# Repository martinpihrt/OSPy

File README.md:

OSPy

###### **O**pen **S**prinkler **Py**thon
OSPy is a free Raspberry Pi based Python 3 program for controlling irrigation systems (sprinkler, drip, IoT, etc). This is my fork from [Rimco/OSPy](https://github.com/Rimco/OSPy) and [Dan-in-CA/SIP](https://github.com/Dan-in-CA/SIP) with My modifications.  

## For first installation and other visit 
[Clean installation](https://github.com/martinpihrt/OSPy/tree/master/ospy/docs/Clean_installation.md)

## Mobile App [Google store](https://play.google.com/store/apps/details?id=com.pihrt.ospy.mobile)

Paired phones and immediate push notifications are managed in **Options → Mobile applications**. Push delivery is disabled by default; the editable relay field is prefilled with the official OSPy relay URL. OSPy sends signed, installation-scoped events asynchronously to the HTTPS relay, which delivers them through Firebase Cloud Messaging. Firebase credentials and FCM device tokens are never stored in OSPy. See the [Mobile API v1 push notification reference](api/docs/Mobile_API_v1.md#immediate-push-notifications).

Normal mobile communication is direct: the Android application connects to the saved local or remote OSPy HTTPS address and uses installation-scoped Mobile API v1 access and refresh tokens to read state and perform permitted actions. Immediate push is a separate background path: OSPy signs an asynchronous request to the configured relay, which validates it and delivers through Firebase Cloud Messaging even while the application is closed. Relay failure cannot block irrigation scheduling or outputs. Both flows are shown in **Diagnostics → How OSPy works**.

The common OSPy footer contains a direct link to the official Android application in Google Play.

When anonymous usage statistics are enabled, OSPy reports the installation UUID, version and non-identifying platform details. On Raspberry Pi it also sends a SHA-256 pseudonym derived locally from the board serial so a reinstallation or replacement SD card is not counted as new hardware. The raw board serial is never transmitted, and systems without a trustworthy board serial omit the hardware identifier.

Refresh-token rotation includes a single short recovery retry for a mobile process terminated between receiving and durably saving its replacement token, such as during a Google Play application update. This preserves saved connections without weakening explicit logout or administrator device revocation.

On supported Android and Google Play services versions, the application also registers a Restore Credential after a successful sign-in. A replacement phone can use the end-to-end encrypted restore key to request a new OSPy token session; passwords, 2FA codes and API tokens are never included in Android backup. OSPy accepts only the production Play signing origin for `com.pihrt.ospy.mobile`, binds each credential to its paired device and invalidates it when that device is revoked. The official Digital Asset Links file must be available at `https://www.pihrt.com/.well-known/assetlinks.json`.

The Android application keeps a persistent device identity for every saved installation. Signing in again to the same installation replaces that device's token session and reuses its OSPy record instead of creating a duplicate. An application reinstall or a genuinely new phone creates a new identity. In OSPy administration, an active device must first be revoked; revoked records can then be permanently deleted individually or together.

The native Android controls also use Mobile API v1 for user water-level adjustment, program-group assignment, a persistent pause between different automatic programs, one-time postponement of a group's next scheduled runs and service-outage management. Refresh-token rotation keeps concurrent foreground and notification requests connected without weakening explicit logout, renewed pairing or administrator device revocation.

Existing irrigation programs support calendar-aware scheduling: allowed months and season shortcuts, odd/even calendar dates, selected days of month, exact or annual excluded ranges, public holidays and global service outages. Native sunrise and sunset program types use the enabled **Sunrise and Sunset** plug-in as their astronomical provider and add an offset, earliest/latest start window and clamp-or-skip policy. Existing programs retain their previous behavior until one of these rules is enabled. See [OSPy Programs](ospy/docs/Programs.md).

The optional **Automation Rules** plug-in builds graphical AND/OR conditions over cached values supplied by monitoring plug-ins, enabled Pihrt or Shelly OSPy sensors, local date/time and read-only OSPy operating states. It supports confirmation and repeat intervals, recovery messages, a safe test mode, detailed history and notifications on OSPy Home, in an open browser, by e-mail, Telegram and native mobile push. A separate default-off control switch enables guarded actions that can stop stations, outputs or running programs, disable the scheduler, operate one output once or in a bounded run/pause cycle in manual mode, change the global water level or invoke an action explicitly declared by another provider. Every cycle transition and its final stop reason is recorded in action history. Compatible providers supply guarded actions: Water Meter resets accumulated counters; Venetian Blind controls movement and tilt; Water Tank Monitor resets extrema or stops regulation; Current Loop Tanks Monitor stops regulation for one or all tanks; and OSPy Backup creates a plug-in data archive. Test mode only simulates actions. Optional incident locking requires an administrator to acknowledge the incident after every condition is available and no longer active; unlocking never reverses an executed action.

The optional **Irrigation Safety** plug-in is a dedicated protection layer over cached Water Meter, Pressure Monitor and tank-provider data plus the actual OSPy output state. It learns a robust expected flow range for each station while that station runs alone, combines configured ranges for simultaneous stations and detects missing, low, high or unexpected flow, missing pressure, low tank level and unavailable measurements. Off, Monitor only and Active protection modes support safe commissioning. Active protection can stop all outputs, switch off the separate master relay, disable the scheduler and continuously enforce an incident lock until an administrator acknowledges the cleared fault. E-mail and native mobile push are delivered asynchronously after the safety action. The responsive page refreshes measurements, active stations, learning progress, incidents and history without a page reload.

The administrator **Diagnostics → System status** card includes a cached background **Operating system health** check for Linux and the root storage device. It verifies the root mount mode, disk space, inodes, a small synchronized write/read probe, accessible EXT4 metadata, Raspberry Pi undervoltage and throttling, temperature, memory, load, failed systemd services and bounded kernel-log evidence of MMC, I/O, EXT4, read-only remount, panic, lockup or out-of-memory failures. Missing commands or permissions are contained and reported without stopping OSPy; the check never runs `fsck` or another repair command on the mounted filesystem.

The built-in administrator retains the original OSPy two-factor settings. Additional accounts are managed on the responsive **Options → Users** page and can independently enable TOTP or e-mail verification from **Account security** after signing in. Existing additional accounts remain compatible and start with 2FA disabled; administrators can reset a lost user pairing without seeing its secret or backup codes.

## Emergency administrator login recovery
If the administrator password is unknown or access to the configured two-factor method has been lost, run the local recovery script from the OSPy directory on the Raspberry Pi or another trusted local shell:

```bash
sudo service ospy stop
sudo python3 back_door.py
sudo service ospy start
```

Stop the service first so its settings database is not being written while recovery runs. The script requires typing `RESET` for confirmation and then generates a new one-time recovery password for the `admin` account. It disables passwordless access and two-factor authentication, removes the TOTP secret and backup codes, revokes remembered browser logins, and invalidates active web sessions after OSPy starts again. Irrigation programs, settings, plug-ins, and logs are not deleted. Open the login page, use the displayed recovery password, change it immediately, and configure two-factor authentication again if required. Use `sudo python3 back_door.py --yes` only in a trusted automated local recovery procedure. See [Clean installation](https://github.com/martinpihrt/OSPy/blob/master/ospy/docs/Clean_installation.md) for more information.

## Hardware relay board test before starting OSPy
The standalone `relay_test.py` script can verify the relay board and GPIO wiring before OSPy is started, or help diagnose a board fault. It switches all eight shift-register relay outputs and the additional main relay output on and off together every 1.5 seconds.

**Warning:** Disconnect pumps, valves, contactors, and any other equipment that must not start unexpectedly. The test energizes every relay. Do not run it while the OSPy service is controlling the same GPIO pins.

From the OSPy directory run:

```bash
sudo service ospy stop
sudo python3 relay_test.py
```

Watch or listen for every relay switching. Stop the test with `Ctrl+C`; the script disables the outputs and cleans up GPIO in its `finally` block. OSPy can then be started normally:

```bash
sudo service ospy start
```

## More information visit
[Pihrt.com](https://pihrt.com/clanky/moje-rapsberry-pi-zavlazovani-zahrady) and [OpenSprinkler](https://opensprinkler.cz  )

YouTube OpenSprinkler channel</br>

## Hardware diagram

## Multisensor ESP32 and Shelly.com
</br>
</br>
[Sensors by Pihrt.com](https://pihrt.com/clanky/esp32-multisnimac-pro-opensprinkler-system)</br>
[Sensors by Shelly.com](https://www.shelly.com/collections/smart-monitoring-saving-energy)

## For translate OSPy to other language
The OSPy system is currently available in multiple languages. For available [languages](https://github.com/martinpihrt/OSPy/tree/master/i18n) and step by step, how to use is typed in MD file
Any user who joins the "OSPy" project is welcome! Translation of strings into other languages is not demanding (using the [Poedit](https://poedit.net/))

## Changelog and Issues
* [Changelog](https://github.com/martinpihrt/OSPy/blob/master/ospy/docs/Changelog.md)
* [Issues](https://github.com/martinpihrt/OSPy/issues)

## Help with to user web Interfaces
* [Czech help page](https://github.com/martinpihrt/OSPy/blob/master/ospy/docs/Web%20Interface%20Guide%20-%20Czech.md)
* [English help page](https://github.com/martinpihrt/OSPy/blob/master/ospy/docs/Web%20Interface%20Guide%20-%20English.md)
* [German help page](https://github.com/martinpihrt/OSPy/blob/master/ospy/docs/Web%20Interface%20Guide%20-%20German.md)
* [Polish help page](https://github.com/martinpihrt/OSPy/blob/master/ospy/docs/Web%20Interface%20Guide%20-%20Polish.md)
* [Russian help page](https://github.com/martinpihrt/OSPy/blob/master/ospy/docs/Web%20Interface%20Guide%20-%20Russian.md)
* [Serbian help page](https://github.com/martinpihrt/OSPy/blob/master/ospy/docs/Web%20Interface%20Guide%20-%20Serbian.md)
* [Slovak help page](https://github.com/martinpihrt/OSPy/blob/master/ospy/docs/Web%20Interface%20Guide%20-%20Slovak.md)

## Communication with other systems
OSPy can be controlled and monitored using HTTP GET commands. With the addition of available plugins OSPy can communicate with other systems via MQTT. OSPy can also issue Linux shell commands when a station is turned on or off. This is useful for controlling wireless remote devices and for I²C relay hats and boards. The Blinker package that is shipped with OSPy sends messages to other Python modules such as plugins to report changes in status. See the signaling examples file in OSPy's plugins folder for examples. Homeassistant integration via MQTT plugin.

## Sensors
OSPy allows to read data from wireless sensors (ESP32, ESP8266...) [Docs](https://github.com/martinpihrt/OSPy/blob/master/hardware_pcb/sensors_pcb_fw/docs/Details.md)
Shelly sensors and periphery [Sensors by Shelly.com](https://www.shelly.com/)
Built-in sensor samples and events remain compatible with the existing local JSON logs and settings stored in OSPy options. When the optional Database Connector plug-in is running and its database responds, each sensor can store history in local JSON, the database, or both, and can independently use JSON or the database for its log page, graph, and CSV exports. Database work is passed through a bounded persistent OSPy queue to a background worker so a slow or unavailable database does not block sensor processing; pending writes and remote deletions survive an OSPy restart, database-only logging falls back to local JSON if the queue cannot accept a record, and sensor deletion is blocked if its durable remote deletion command cannot be queued safely.

## Remote Controller for OSPy based on M5stick-C 
This controller allows you to select a program stored in the OSPy on the LCD display and start it with the button. The controller is connected to the home Wi-Fi network. We do not even need a mobile phone or a computer to quickly select programs. We will use this miniature controller. [Docs](https://github.com/martinpihrt/OSPy/blob/master/hardware_pcb/remote_controllers_fw/docs/Details.md)

## License
OpenSprinkler Py (OSPy) Interval Program
Creative Commons Attribution-ShareAlike 3.0 license

## Acknowledgements
Full credit goes to Dan for his generous contributions in porting the microcontroller firmware to Python.
* The program makes use of web.py (http://webpy.org) for the web interface.
* The program makes use of cmarkgfm (https://github.com/theacodes/cmarkgfm) to render the help pages written in GitHub flavored markdown (Python 3+).
* The program makes use of OpenStreetMap (https://www.openstreetmap.org) to convert locations into coordinates.
* Interactive weather location maps use Leaflet 1.9.4 (https://leafletjs.com), distributed locally under the BSD 2-Clause license, with map tiles and attribution from OpenStreetMap.
* The program makes use of Stormglass API (https://stormglass.io/) for weather information.
* The program makes use Blinker (https://pythonhosted.org/blinker/) package that is shipped with OSPy sends messages to other Python modules such as plugins to report changes in status.
* The program makes use Arduino (https://arduino.cc) ESP32, Atmega328 and more HW boards pro OSPy aditional sensors, water tank monitor.

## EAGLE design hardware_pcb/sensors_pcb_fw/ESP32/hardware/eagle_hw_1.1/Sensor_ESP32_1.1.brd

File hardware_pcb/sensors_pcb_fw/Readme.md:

OSPy Sensors Readme 
====

## More information visit
[pihrt.com Martin Pihrt website](https://pihrt.com/) and [Arduino core for the ESP32 website](https://github.com/espressif/arduino-esp32)

INSTALLATION:
===========

### Arduino IDE in operating system (Linux or Windows)
- Install the current upstream Arduino IDE at the 1.8 level or later. The current version is at the [Arduino website](http://www.arduino.cc/en/main/software).
- Start Arduino and open Preferences window.
- Enter one of the release links above into *Additional Board Manager URLs* field. You can add multiple URLs, separating them with commas.
- Open Boards Manager from Tools > Board menu and install *esp32* platform (and don't forget to select your ESP32 board from Tools > Board menu after installation).
- Extract the OneWire and Dallas Temperature folders from the esp32/library folder. Then copy the folders to your arduino library location. Example: documents/arduino/libraries
- More infos with images is here: https://pihrt.com/elektronika/439-ospy-jak-pridat-a-pripojit-snimace

## Acknowledgements
Arduino IDE software (https://arduino.cc).
Arduino core for the ESP32 website (https://github.com/espressif/arduino-esp32).
DS18B20 libraries (https://www.arduinolibraries.info/libraries/dallas-temperature).
OneWire libraries (https://www.arduinolibraries.info/libraries/one-wire).

Sensor FW Changelog
====

FW: 1.02
-----------
(martinpihrt)<br/>
Changes:<br/>
Add AP manager for settings sensor from phone, tablet (4 minutes timeout). For run AP manager: push button least > 2 seconds. Password for AP Wi-Fi is "ospy-sensor-esp32", next open browser and type IP "192.168.1.1".<br/>
Add saving to eeprom memory. Fast blinking LED if AP manager. Slow blinking LED if normal run.<br/>
Add control relay from stations: ex: http://IP/securecode?re=1 (or re=0). In AP manager is active button  for control relay ON or OFF. Available only on the same network as OSPy.

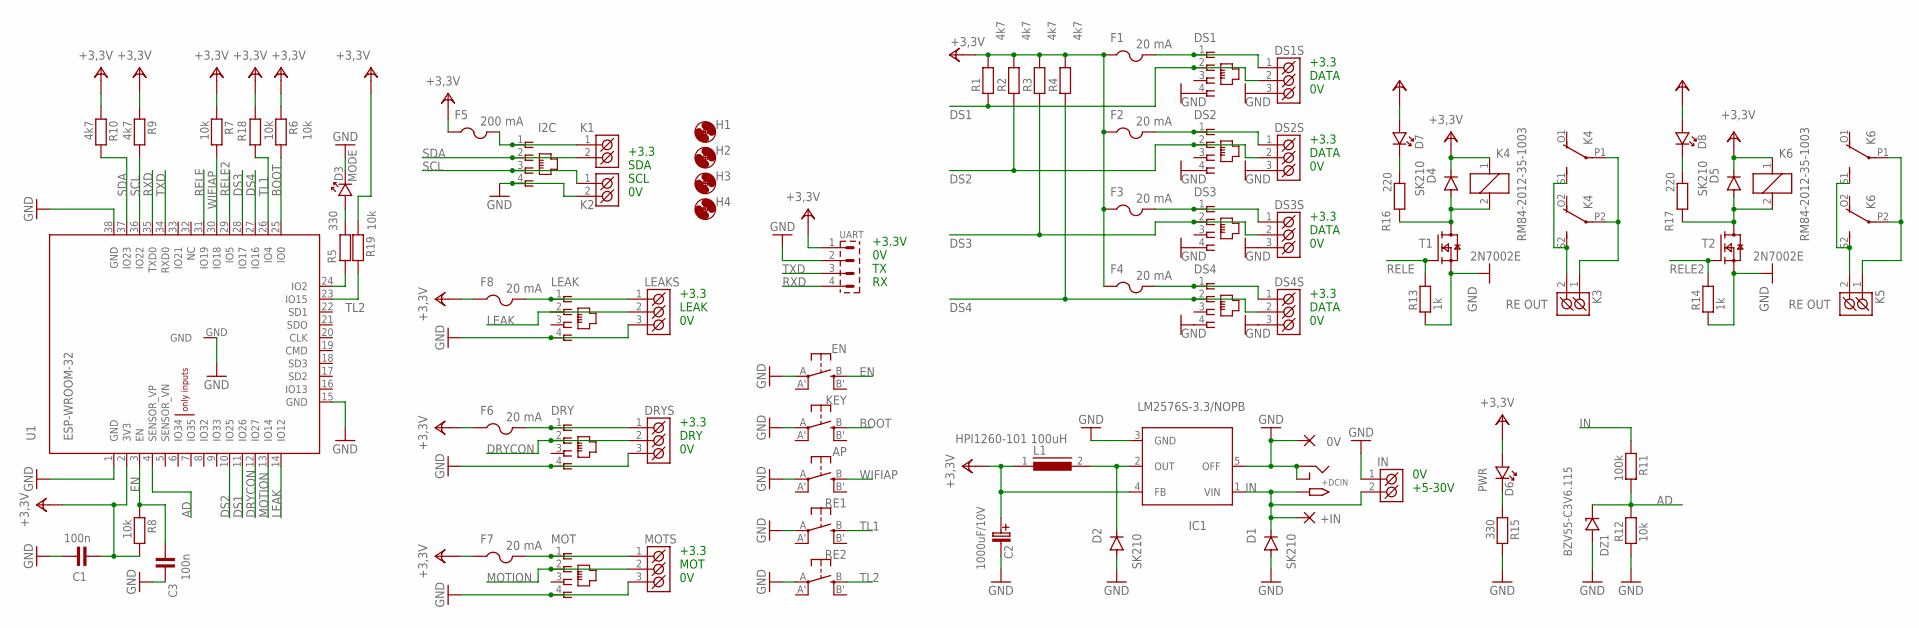
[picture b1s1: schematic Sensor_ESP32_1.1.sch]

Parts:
0V: SMD2; SMD1,27-2,54
+DCIN: 2.1MMJACKTHM; PJ-102A
+IN: SMD2; SMD1,27-2,54
AP: SPST_TACT-EVQQ2; EVQ-Q2
C1, C3: 100n; 1206
C2: 1000uF/10V; C-EL_5
D1, D2, D4, D5: SK210; SMB
D3: MODE; P1206
D6: PWR; P1206
D7, D8: LED_1206; P1206
DRY: WEBP_6_1
DRYS: ARK550/3
DS1, DS2, DS3, DS4: WEBP_6_1
DS1S, DS2S, DS3S, DS4S: ARK550/3
DZ1: BZV55-C3V6.115; SOD-80
EN: SPST_TACT-EVQQ2; EVQ-Q2
F1, F2, F3, F4, F6, F7, F8: 20 mA; R1206
F5: 200 mA; R1206
H1, H2, H3, H4: MOUNT-HOLE3.0; 3,0
I2C: WEBP_6_1
IC1: LM2576S-3.3/NOPB; TO263-5
IN: ARK550/2
K1, K2: ARK550/2
K3, K5: RE OUT; ARK500/2
K4, K6: RM84-2012-35-1003; G2R2
KEY: SPST_TACT-EVQQ2; EVQ-Q2
L1: HPI1260-101 100uH; DR125
LEAK: WEBP_6_1
LEAKS: ARK550/3
MOT: WEBP_6_1
MOTS: ARK550/3
R1, R2, R3, R4, R9, R10: 4k7; 1206
R5, R15: 330; 1206
R6, R7, R8, R12, R18, R19: 10k; 1206
R11: 100k; 1206
R13, R14: 1k; 1206
R16, R17: 220; 1206
RE1, RE2: SPST_TACT-EVQQ2; EVQ-Q2
T1, T2: 2N7002E; SOT23
U1: ESP-WROOM-32
UART: S1G4_JUMP; S1G4_JUM

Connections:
+3,3V: C1.2, C2.C+ (C_EL+), D4.C, D5.C, D6.A, D7.A, D8.A, F1.1, F2.1, F3.1, F4.1, F5.1, F6.1, F7.1, F8.1, IC1.4 (FB), K4.1, K6.1, L1.1, R1.2, R2.2, R3.2, R4.2, R6.1, R7.1, R8.2, R9.1, R10.1, R18.1, R19.1, U1.2 (3V3), UART.1
AD: DZ1.K, R11.2, R12.2, U1.4 (SENSOR_VP)
BOOT: KEY.B (S), R6.2, U1.25 (IO0)
DRYCON: DRY.2, DRYS.2 (K2), U1.12 (IO27)
DS1: DS1.2, DS1S.2 (K2), R1.1, U1.11 (IO26)
DS2: DS2.2, DS2S.2 (K2), R2.1, U1.10 (IO25)
DS3: DS3.2, DS3S.2 (K2), R3.1, U1.28 (IO17)
DS4: DS4.2, DS4S.2 (K2), R4.1, U1.27 (IO16)
EN: C3.2, EN.B (S), R8.1, U1.3 (EN)
GND: 0V.1, +DCIN.RING, +DCIN.RING_SW, AP.A, C1.1, C2.C- (C_EL-), C3.1, D1.A, D2.A, D3.K, DRY.4, DRYS.3 (K3), DS1.4, DS1S.3 (K3), DS2.4, DS2S.3 (K3), DS3.4, DS3S.3 (K3), DS4.4, DS4S.3 (K3), DZ1.A, EN.A, I2C.4, IC1.3 (GND), IC1.5 (OFF), IN.1 (K1), K2.2 (K2), KEY.A, LEAK.4, LEAKS.3 (K3), MOT.4, MOTS.3 (K3), R12.1, R13.1, R14.1, R15.2, RE1.A, RE2.A, T1.2 (S), T2.2 (S), U1.1 (GND), U1.15 (GND), U1.38 (GND), U1.GND, UART.2
IN: +DCIN.TIP, +IN.1, D1.C, IC1.1 (VIN), IN.2 (K2), R11.1
LEAK: LEAK.2, LEAKS.2 (K2), U1.14 (IO12)
MOTION: MOT.2, MOTS.2 (K2), U1.13 (IO14)
unnamed: DS1.1, DS1S.1 (K1), F1.2
unnamed: D2.C, IC1.2 (OUT), L1.2
unnamed: DS2.1, DS2S.1 (K1), F2.2
unnamed: F8.2, LEAK.1, LEAKS.1 (K1)
unnamed: DS3.1, DS3S.1 (K1), F3.2
unnamed: DS4.1, DS4S.1 (K1), F4.2
unnamed: F5.2, I2C.1, K1.1 (K1)
unnamed: D4.A, K4.2, R16.2, T1.3 (D)
unnamed: R5.2, U1.24 (IO2)
unnamed: K3.2 (K2), K4.S1 (S), K4.S2 (S)
unnamed: K3.1 (K1), K4.P1, K4.P2
unnamed: DRY.1, DRYS.1 (K1), F6.2
unnamed: F7.2, MOT.1, MOTS.1 (K1)
unnamed: D5.A, K6.2, R17.2, T2.3 (D)
unnamed: K5.2 (K2), K6.S1 (S), K6.S2 (S)
unnamed: K5.1 (K1), K6.P1, K6.P2
unnamed: D6.K, R15.1
unnamed: D3.A, R5.1
unnamed: D7.K, R16.1
unnamed: D8.K, R17.1
RELE: R13.2, T1.1 (G), U1.31 (IO19)
RELE2: R14.2, T2.1 (G), U1.29 (IO5)
RXD: U1.35 (TXD0), UART.4
SCL: I2C.3, K2.1 (K1), R9.2, U1.36 (IO22)
SDA: I2C.2, K1.2 (K2), R10.2, U1.37 (IO23)
TL1: R18.2, RE1.B (S), U1.26 (IO4)
TL2: R19.2, RE2.B (S), U1.23 (IO15)
TXD: U1.34 (RXD0), UART.3
WIFIAP: AP.B (S), R7.2, U1.30 (IO18)

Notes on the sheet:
+3.3 SDA SCL 0V
+3.3 DATA 0V
0V +5-30V
+3.3V 0V TX RX
+3.3 DRY 0V
+3.3 MOT 0V
+3.3 LEAK 0V

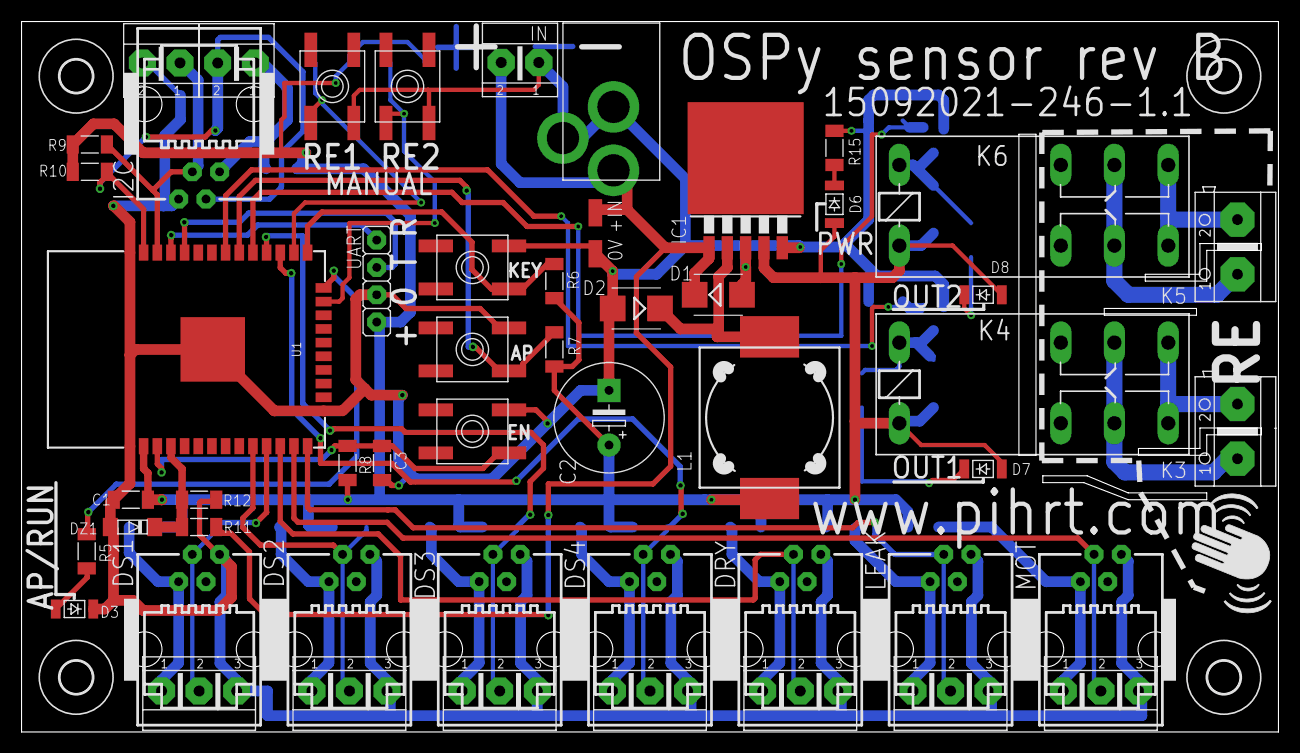
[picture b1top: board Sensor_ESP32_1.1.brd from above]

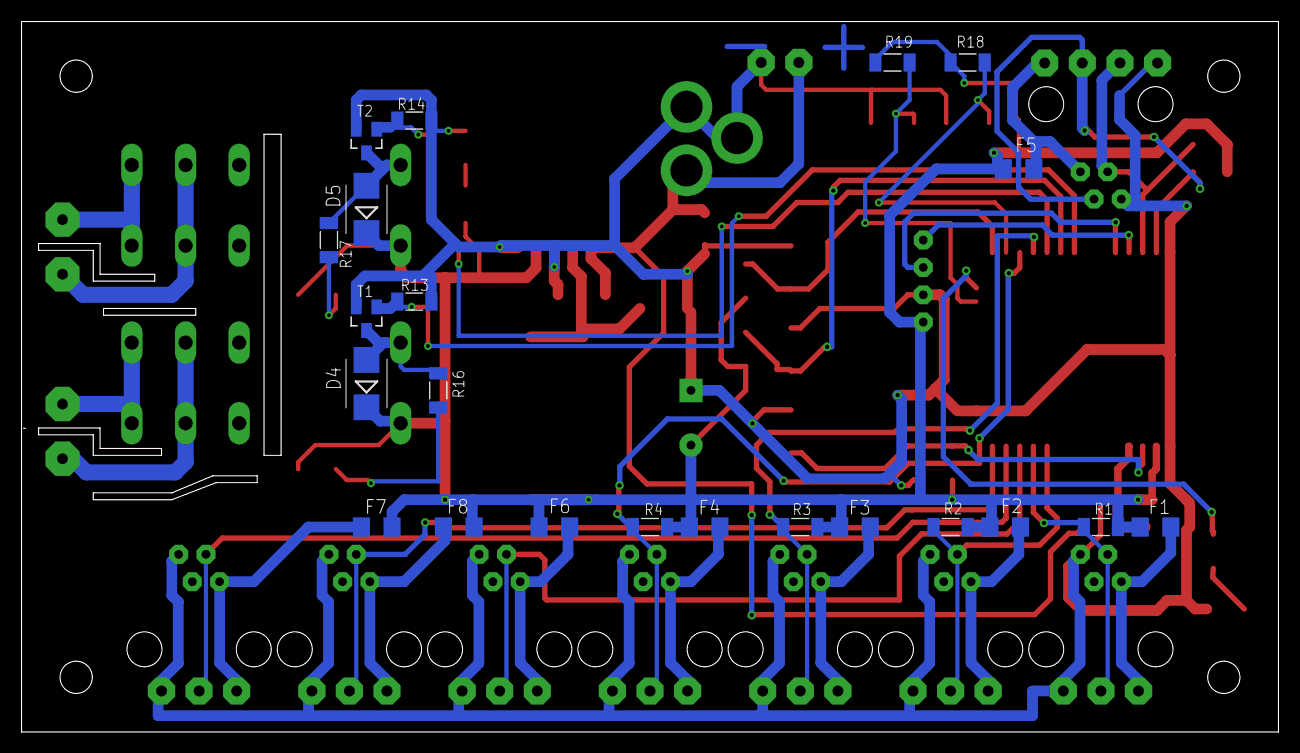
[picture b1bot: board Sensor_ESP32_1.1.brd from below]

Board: 2 copper layers, 116.8 x 66.0 mm, 80 parts (22 on the bottom side), 42 nets.

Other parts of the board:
U$1: GESTURESENSE_NOTEXT

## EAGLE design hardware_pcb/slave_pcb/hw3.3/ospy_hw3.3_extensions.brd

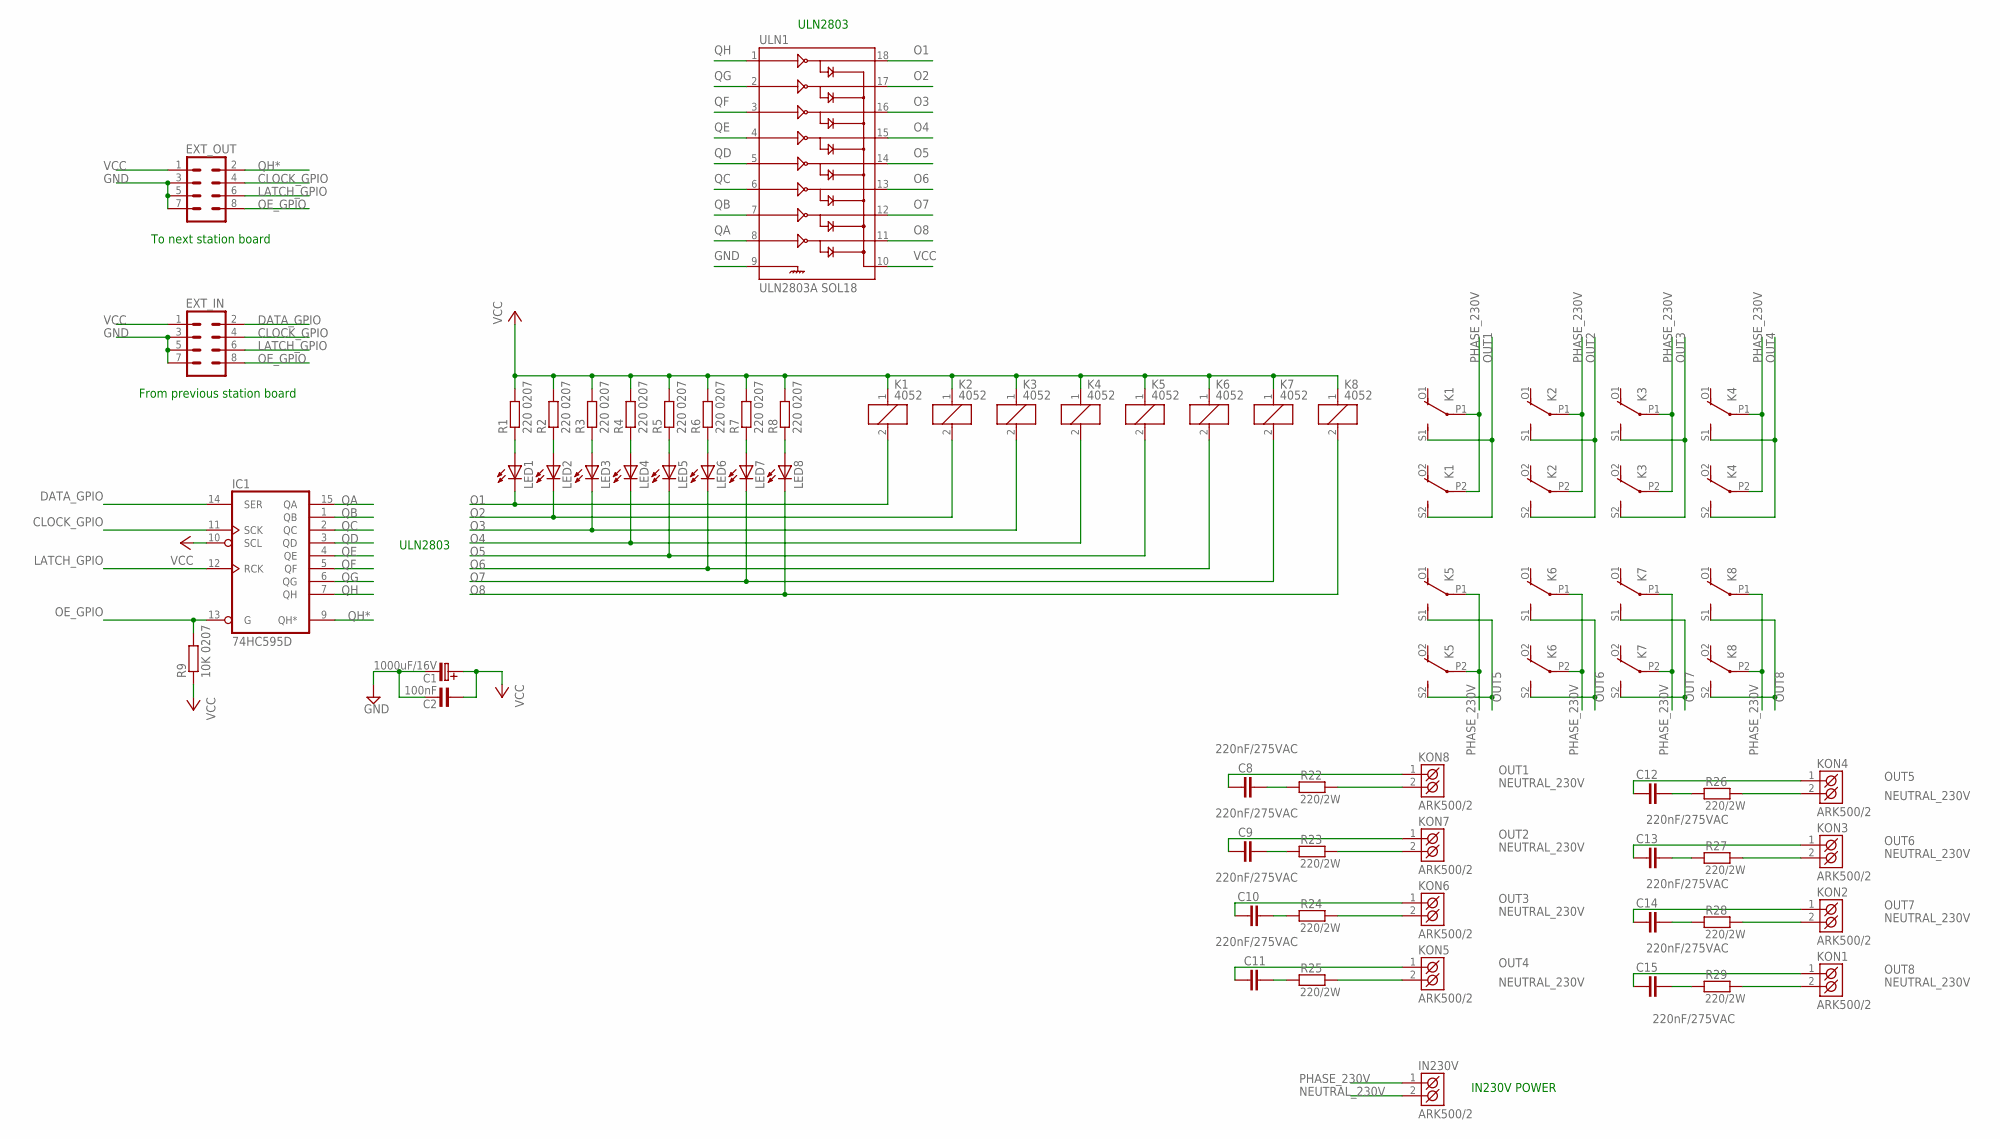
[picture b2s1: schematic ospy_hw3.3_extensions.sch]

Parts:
C1: 1000uF/16V; C_EL_5
C2: 100nF; RM5_2,5
C8, C9, C10, C11, C12, C13, C14, C15: 220nF/275VAC; C225-087X268
EXT_IN: M04X2; 2X4
EXT_OUT: M04X2; 2X4
IC1: 74HC595D; SO16
IN230V: ARK500/2
K1, K2, K3, K4, K5, K6, K7, K8: 4052; F4052
KON1, KON2, KON3, KON4, KON5, KON6, KON7, KON8: ARK500/2
LED1, LED2, LED3, LED4, LED5, LED6, LED7, LED8: LED3MM
R1, R2, R3, R4, R5, R6, R7, R8: 220 0207; 0207/10
R9: 10K 0207; 0207/10
R22, R23, R24, R25, R26, R27, R28, R29: 220/2W; R__2W
ULN1: ULN2803A SOL18; SO18L

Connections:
CLOCK_GPIO: EXT_IN.4, EXT_OUT.4, IC1.11 (SCK)
DATA_GPIO: EXT_IN.2, IC1.14 (SER)
GND: C1.C- (C_EL-), C2.2, EXT_IN.3, EXT_IN.5, EXT_IN.7, EXT_OUT.3, EXT_OUT.5, EXT_OUT.7, IC1.8 (GND), ULN1.9
LATCH_GPIO: EXT_IN.6, EXT_OUT.6, IC1.12 (RCK)
unnamed: LED1.A, R1.1
unnamed: LED2.A, R2.1
unnamed: LED3.A, R3.1
unnamed: LED4.A, R4.1
unnamed: LED5.A, R5.1
unnamed: LED6.A, R6.1
unnamed: LED7.A, R7.1
unnamed: LED8.A, R8.1
unnamed: C10.2, R24.1
unnamed: C9.2, R23.1
unnamed: C8.2, R22.1
unnamed: C11.2, R25.1
unnamed: C12.2, R26.1
unnamed: C13.2, R27.1
unnamed: C14.2, R28.1
unnamed: C15.2, R29.1
NEUTRAL_230V: IN230V.2 (K2), KON1.2 (K2), KON2.2 (K2), KON3.2 (K2), KON4.2 (K2), KON5.2 (K2), KON6.2 (K2), KON7.2 (K2), KON8.2 (K2), R22.2, R23.2, R24.2, R25.2, R26.2, R27.2, R28.2, R29.2
O1: K1.2, LED1.K (C), ULN1.18
O2: K2.2, LED2.K (C), ULN1.17
O3: K3.2, LED3.K (C), ULN1.16
O4: K4.2, LED4.K (C), ULN1.15
O5: K5.2, LED5.K (C), ULN1.14
O6: K6.2, LED6.K (C), ULN1.13
O7: K7.2, LED7.K (C), ULN1.12
O8: K8.2, LED8.K (C), ULN1.11
OE_GPIO: EXT_IN.8, EXT_OUT.8, IC1.13 (G), R9.2
OUT1: C8.1, K1.S1 (S), K1.S2 (S), KON8.1 (K1)
OUT2: C9.1, K2.S1 (S), K2.S2 (S), KON7.1 (K1)
OUT3: C10.1, K3.S1 (S), K3.S2 (S), KON6.1 (K1)
OUT4: C11.1, K4.S1 (S), K4.S2 (S), KON5.1 (K1)
OUT5: C12.1, K5.S1 (S), K5.S2 (S), KON4.1 (K1)
OUT6: C13.1, K6.S1 (S), K6.S2 (S), KON3.1 (K1)
OUT7: C14.1, K7.S1 (S), K7.S2 (S), KON2.1 (K1)
OUT8: C15.1, K8.S1 (S), K8.S2 (S), KON1.1 (K1)
PHASE_230V: IN230V.1 (K1), K1.P1, K1.P2, K2.P1, K2.P2, K3.P1, K3.P2, K4.P1, K4.P2, K5.P1, K5.P2, K6.P1, K6.P2, K7.P1, K7.P2, K8.P1, K8.P2
QA: IC1.15 (QA), ULN1.8
QB: IC1.1 (QB), ULN1.7
QC: IC1.2 (QC), ULN1.6
QD: IC1.3 (QD), ULN1.5
QE: IC1.4 (QE), ULN1.4
QF: IC1.5 (QF), ULN1.3
QG: IC1.6 (QG), ULN1.2
QH: IC1.7 (QH), ULN1.1
QH*: EXT_OUT.2, IC1.9 (QH*)
VCC: C1.C+ (C_EL+), C2.1, EXT_IN.1, EXT_OUT.1, IC1.10 (SCL), IC1.16 (VCC), K1.1, K2.1, K3.1, K4.1, K5.1, K6.1, K7.1, K8.1, R1.2, R2.2, R3.2, R4.2, R5.2, R6.2, R7.2, R8.2, R9.1, ULN1.10

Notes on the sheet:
ULN2803
IN230V POWER
To next station board
From previous station board

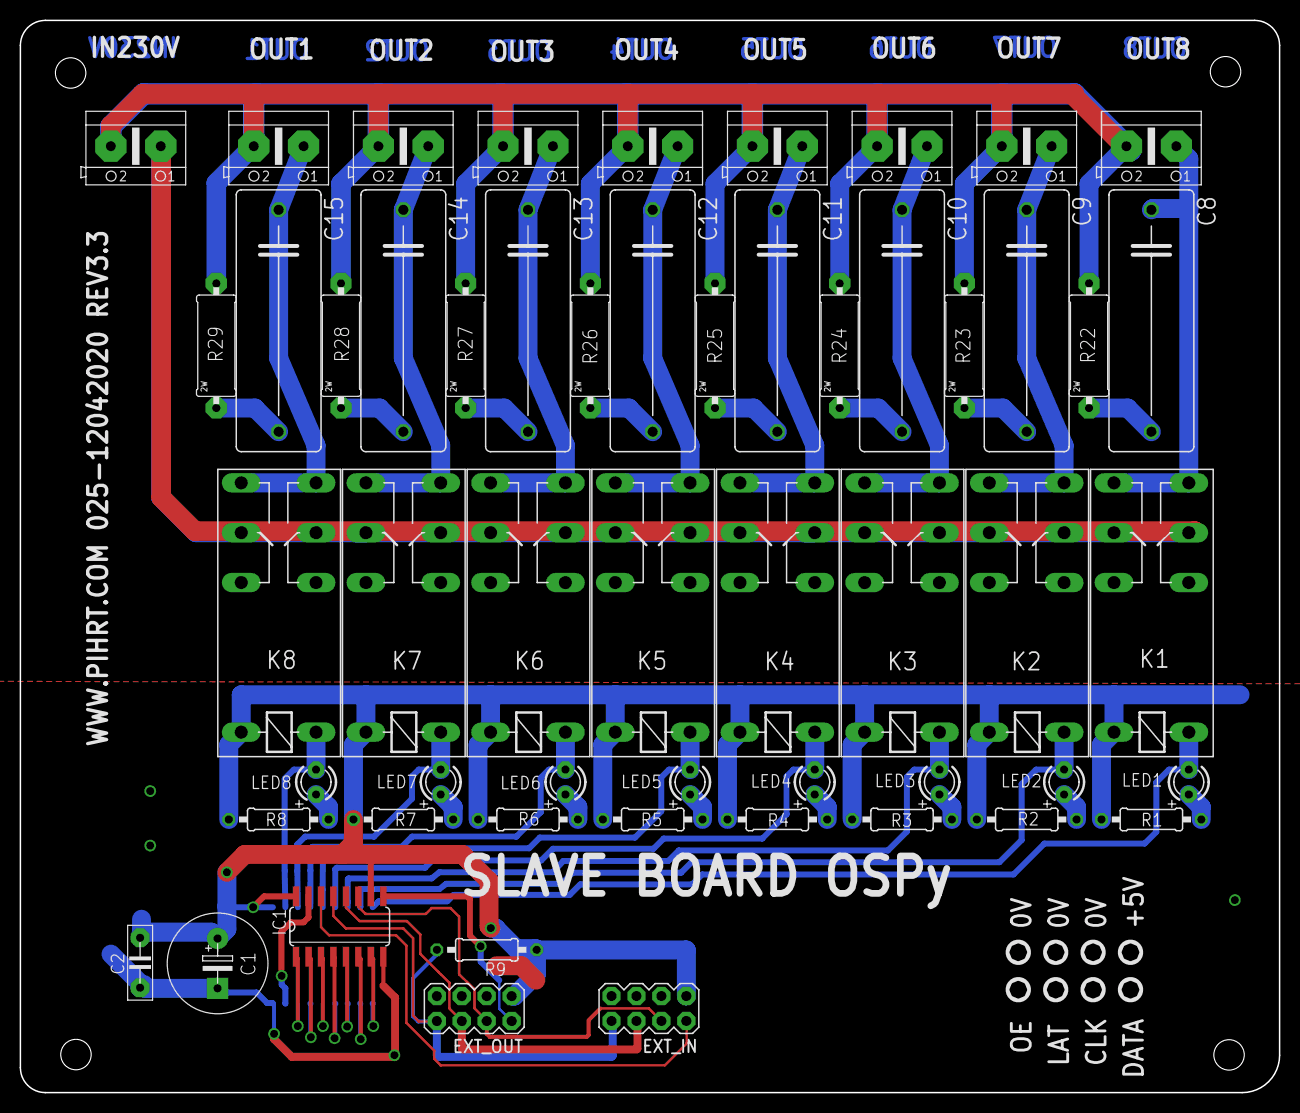
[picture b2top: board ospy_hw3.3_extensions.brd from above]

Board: 2 copper layers, 128.3 x 109.2 mm, 56 parts (1 on the bottom side), 49 nets.

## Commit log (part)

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2022-06-08 Fix in plugin "air temperature" (regulation time mm:ss) and added new function in plugin "pool heating" (safety shutdown. Simply put, if the temperature is higher and it takes xx minutes then it mean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
2022-06-15 Add new plugin "Email Notifications SSL". This extension is a more modern variant of the original E-mail Notifications (secured with SSL Connection) extension. This extension is for Python 3 only. Al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
2022-06-24 Czech language strings update. Add new plugin "Astro sunrise and sunset". This extension allows you to run a specific program depending on sunrise or sunset. This extension calculate the following as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
2022-06-24 Lang update
2022-06-28 Plugin "tank monitor" added new FW 1.4 for CPU atmega with crc8 calculation, "astro sunrise and sunset" added menu for selecting programs to run. Czech language update.
2022-07-11 Corrections in OSPy settings: OSPy backup to zip, restore from zip, delete to default. Update of the translation in the Czech language. After this update, it is necessary to create a new backup (in t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
2022-07-19 Added automatical login (in OSPy options under user). Browser remembers your login information and logs you in. Added enter support on login page (username or password field must be focused).
2022-07-26 Czech language strings update. Add new plugin "Photovoltaic Boiler". PV boiler (heating boiler from the distribution network or FVE power plant). Must be tested.
2022-08-02 Fix print IP address in Linux 5.15.32-v7+, armv7l, Python 3.9.2
2022-08-18 Updating the Czech language. Added new plugin "IP CAM". Fix in "pressurizer" plugin.
2022-08-25 Fixed problems on the home page (admin, user, public) with the display of values from sensors (if there were more sensors, not all of them were displayed). Added new plugin "Modbus Stations" (under c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
2022-09-09 Updating the Slovak language (thank you Tomáš Szepesi).
2022-09-13 Updating the Czech and Slovak language. Fixed error in stations in python 3 (when the number of stations is changed and the master station is not used). The modbus station extension is tested and rea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
2023-05-02 Fixed service startup in Python 3. Dark Sky API - support for the Dark Sky API will has ended on March 31st, 2023. Dark Sky API is newly replaced by stormglass.io API (The service is free for 10 call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
2023-05-24 Added Wi-Fi signal level and power supply voltage logging to multisensors in OSPy (logging to graph).
2023-07-01 Fixed a bug with the window about available updates popping up on the home page. When the update check is turned off in the plugins settings, the notification window will not pop up on the home page.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
2023-07-11 Updating the Czech language (new strings). Tested new plugin CHMI. Added new function to wind speed plugin (not tested yet). Removed python 2 dependency from all plugins.
2023-07-26 Updating the Czech language (new strings). Bug fixed: if the program is running and a time rain delay occurs, the station did not turn off.
2023-07-30 Updating the Czech language (new strings) for new CHMI plugin. Example is here: https://github.com/martinpihrt/OSPy-plugins/blob/master/plugins/chmi/static/images/meteomap.png. The plugin can detect 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
2023-08-01 Added get function to /api/balances and /api/pluginfooter (for future use in the mobile application). More doc in OSPy help API Details.md.
2023-08-04 Updating the Czech language (new strings) for CHMI plugin (added logging).
2023-08-11 Updating the Czech language (new strings). Added new plugin "Label Maker" (creation of EAN and QR codes for subsequent printing). Added post function to /api/runonce (Allows you to start the selected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
2023-08-13 Updating the Czech language (new strings). Fix error in api/options. Fix error in MQTT run-once plugin. Add doc with images to MQTT run-once plugin.
2023-08-15 Fixed wrong timestamp in API/logs
2024-02-22 Updating the Czech language. Added new plugin "IP Scanner" and "Database Connector". Removing the AES key function from the sensor (now no longer required or verified by the AES key when sensor inser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
2024-04-20 Updating the Czech language (new strings) for new ospy backup plugin. Added new plugin "ospy backup". This extension creates a backup of data directories from all available installed extensions in OS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
2024-06-27 OSPy - fixed installation error (sudo python3 setup.py install) cmarkgfm, added requirements, paho-mqtt, mariadb. Prepare for home assistant integration: (helpers - Fully qualified domain name, get r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
2024-07-03 OSPy - updating the Czech language (new and updated strings) for new MQTT Home Assistant plugin (So far only a broken test! Do not use!).
2024-07-19 Added installation script for easier installation of OSPy. Now you just need to log into your Raspberry pi via SSH and run the script. The script will run the installation wizard and then download th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
2024-07-19 script address
2024-08-04 Update signaling plugin (add new signal 30s tick, add new signal airtemphumy updated, add automatic log in textarea). Finished plugin "Home Assistant" for MQTT itegration (With air temp plugin itegra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
2024-08-12 The back_door.py file has been added to the OSPy folder, which allows logging into OSPy in case we cannot log in (or do not know the password). We will not lose the settings and log history in OSPy a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
2024-08-13 Modification of installation script (ospy_setup.sh) -> added option to install sql connector (for sql connector plugin). Update of Czech language strings. In pressure monitor plugin added option to l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
2024-09-01 Updating the Czech language. From jonathan marsh was imported the function for to inject base.html from any plugin. This gives us the ability to inject our own script from any plugin and modify the h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
2024-09-03 Updating the Czech language. Bug fix: internal server 500 error in OSPy options (if you reboot or restart hw OSPy with the button).
2024-11-01 Added 2PM addon device support to device selection in Shelly integration plugin. Working on a new plugin for level measurement using pressure change (sensor input 4-20mA).
2024-11-06 Updating the Czech language. New plugin: Current Loop Tanks Monitor is ready to use (no possibility of automation yet - measurement and logswork is ready).
2024-12-30 Updating the Czech language. Fixed broken language change in OSPy options (the change was not saved and thus the language did not change). Added device loading over local network (cloud or local netw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
2025-01-02 Updating the Czech language. The Shelly integration plugin is already loaded in OSPy in the sensor search section. Fix for plugin listings in the footer on the homepage (now there will be no more dup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
2025-01-08 Czech language update. Fixed exceptions on the web in the session (web/sessions.py). If we search for Shelly in OSPy sensors and click the create button, a new sensor will be created in the sensors a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
2025-01-16 Czech language update. Parameters (programs and events) can already be set in the sensors (shelly), data is displayed on the home page. Triggering and recording are not yet functional. This is being 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
2025-01-27 Fix in logging for Shelly in OSPy sensors. Czech language update.
2025-02-06 Updating the Slovak language (thank you Tomáš Szepesi). Added css style for switches in the "astral" plugin. Added documentation (calibration) to the help in the "current 4 tank" plugin.
2025-02-26 Czech language update. Updated docs in czech and english page (https://github.com/martinpihrt/OSPy/tree/master/ospy/docs). Updating the Slovak language (thank you Tomáš Szepesi). Added pycache_clean.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
2025-03-31 Czech language update. Update plugin: Shelly integration plugin (added Shelly Pro 3EM -> three-phase energy meter. Cloud OK, Local not ready).
2025-04-03 Czech language update. Update plugin: Shelly integration plugin (updated Shelly Pro 3EM -> three-phase energy meter. Cloud read data OK, Local read data OK). Now we can also read data from the Pro 3E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
2025-06-30 Czech language update. Update plugin: Shelly integration plugin (fixed Client has sent too many requests in a given amount of time). Fixed OSPy sensors (sensor state_machine as 'high', 'low', 'normal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
2025-07-01 Fixed OSPy home Delete all parallel rain blocks (e.g. from CHMI plugin, current loop tank monitor...) When an extension set a rain delay, it could not be cancelled on the home page (it had to be canc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
2025-10-25 Fixed a bug with logging in multisensors (in case of a temperature drop, continuous logging occurred).
2025-10-28 Czech language update. Added rollback function to system update plugin (10 levels back).
2025-10-31 Czech language update. Network Ping Monitor is ready for using.
2025-11-04 New script for HW testing relay on board (in OSPy folder). If you need to test the hardware board (to see if all relays are switching—e.g., in case of a hardware problem with the relays), stop the se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
2026-06-26 Czech language update. New weather dashboard plugin (not everything has been tested).
2026-06-26 Czech language update. New weather dashboard plugin (not everything has been tested). Added hot start/stop/reload handling for plugins from the plugin manager, so an enabled or updated plugin can be 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
2026-06-27 Plugin update checking is now triggered immediately after changing the update switches in the plugin manager, and repository downloads use a timeout. The home page update notification modal was impro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
2026-06-27 The Run Once page now shows a separate read-only live countdown for active run-once stations, updated from the status API without requiring a page refresh.
2026-06-27 Manual mode on the home page now also shows a separate read-only live countdown next to the manual station timer fields, with remaining time supplied by the status API.
2026-06-27 Fix plugin changes freshness and display
    Plugin update checking is now triggered immediately after changing the update switches in the plugin manager, and repository downloads use a timeout. The home page update notification modal was impro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
2026-06-27 Czech language translation template was regenerated with updated core and plugin strings.
2026-06-28 Security hardening: added brute-force protection for web and API password checks, including per IP and username throttling, temporary lockout after repeated failed attempts, and constant-time passwor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
2026-06-28 Add program groups and conflict warnings
2026-06-29 Update web interface guides and add Slovak version
2026-06-29 Add program groups and improve program UI
2026-06-29 Czech langugage for new strings.
2026-06-29 Move shared I2C guard into plugin package directory
2026-06-29 Move shared I2C guard into OSPy core namespace
2026-06-29 Prepared language support for German, Polish, Serbian, and Russian, including placeholder gettext catalogs based on English. Added web interface guide documents for German, Polish, Serbian, and Russi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
2026-06-29 Added po files for translating
2026-06-30 Enforce CSRF for plugin POST requests
2026-06-30 Clarify station pause and master offset settings help. Improve options label layout for long translations
2026-06-30 Added compatibility for newer Python versions by providing a local fallback for the removed cgi module used by web.py form handling, while keeping Python 3.11 behavior unchanged. Replaced the removed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
2026-06-30 Hardened the Raspberry Pi installation script with safer shell options, whiptail bootstrapping, quoted install paths, guarded i2c and user-group setup, safer systemd service generation, daemon reload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
2026-06-30 Session cookies now use the Secure flag automatically when OSPy starts with a valid HTTPS certificate, while remaining compatible with HTTP-only installations.
2026-06-30 The web login now regenerates the session id after successful password verification to reduce session fixation risk while preserving the current session data.
2026-06-30 API CORS handling is now centralized and configurable through the Security options, including support for a specific allowed origin list or disabling CORS headers, and legacy JSONP responses are disa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
2026-06-30 Plugin install and update actions now show the exact source repository before confirmation, log the selected source, display a checking status while loading remote changes, and validate ZIP extractio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
2026-06-30 The local back_door.py recovery script now warns before resetting credentials, requires confirmation unless --yes is used, disables passwordless access, revokes remembered browser logins, and uses a 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
2026-06-30 Translation updates in all languages

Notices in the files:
parts and their libraries:
Copyright (C) PaJa 2001-2014
Copyright (C) PaJa 2011-2014
SparkFun-Aesthetics: Licensing: Creative Commons ShareAlike 4.0 International - https://creativecommons.org/licenses/by-sa/4.0
Copyright (C) PaJa 2003-2009
